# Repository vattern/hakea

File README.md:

# hakea

.

To flash the bootloader :
```
cd bootloader
openocd -f hakea.cfg
```

Current version : 1.0.4

This work is licensed under a
[Creative Commons Attribution-NonCommercial-ShareAlike 4.0 International License][cc-by-nc-sa].

[![CC BY-NC-SA 4.0][cc-by-nc-sa-image]][cc-by-nc-sa]

[cc-by-nc-sa]: http://creativecommons.org/licenses/by-nc-sa/4.0/
[cc-by-nc-sa-image]: https://licensebuttons.net/l/by-nc-sa/4.0/88x31.png
[cc-by-nc-sa-shield]: https://img.shields.io/badge/License-CC%20BY--NC--SA%204.0-lightgrey.svg

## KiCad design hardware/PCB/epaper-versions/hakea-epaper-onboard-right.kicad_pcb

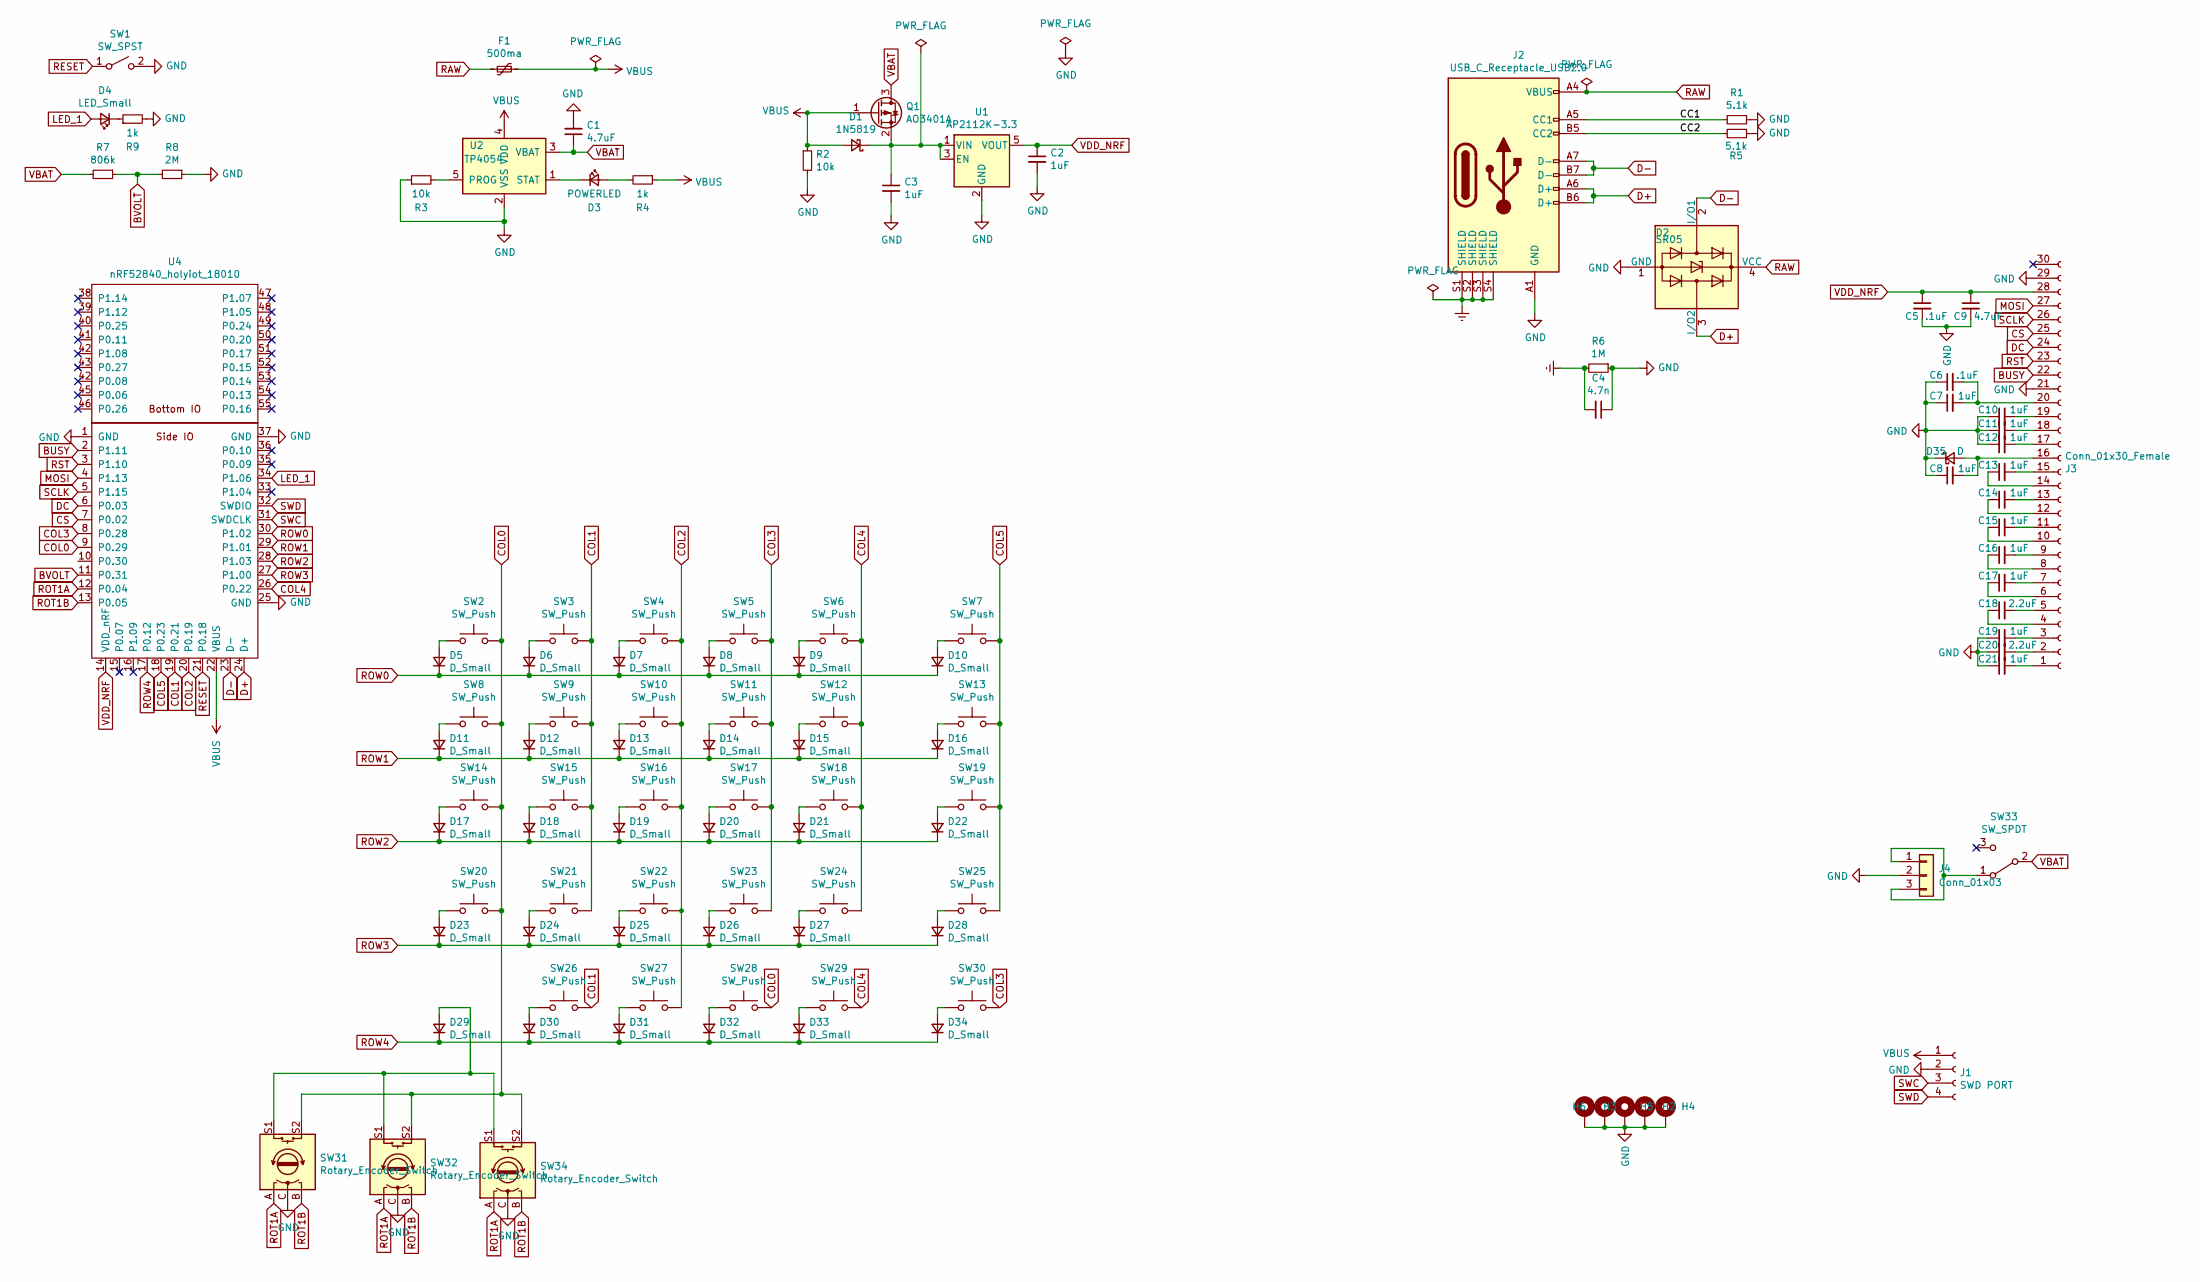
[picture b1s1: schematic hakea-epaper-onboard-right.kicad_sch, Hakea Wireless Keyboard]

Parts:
C1: 4.7uF; C_0805_2012Metric
C2, C3: 1uF; C_0805_2012Metric
C4: 4.7n; C_1206_3216Metric
C5, C6: .1uF; C_0402_1005Metric; LCSC C1525
C7, C8, C10, C11, C12, C13, C14, C15, C16, C17, C19, C21: 1uF; C_0402_1005Metric; LCSC C52923
C9: 4.7uF; C_0402_1005Metric; LCSC C23733
C18, C20: 2.2uF; C_0603_1608Metric; LCSC C23630
D1: 1N5819; D_SOD-123
D2: SR05; SOT-143
D3: POWERLED; D_0805_2012Metric
D4: LED_Small; D_0805_2012Metric
D5, D6, D7, D8, D9, D10, D11, D12, D13, D14, D15, D16, D17, D18, D19, D20, D21, D22, D23, D24, D25, D26, D27, D28, D29, D30, D31, D32, D33, D34: D_Small; D_SOD-123
D35: D; D_SOD-123; LCSC C8598
F1: 500ma; Fuse_1206_3216Metric
H2, H3, H4, H5, H6: MountingHole; MountingHole_2.2mm_M2_ISO7380_Pad
J1: SWD PORT; PinHeader_1x04_P2.54mm_Vertical
J2: USB_C_Receptacle_USB2.0; USB-C_C168688; LCSC Part C168688
J3: Conn_01x30_Female; Hirose_FH12-30S-0.5SH_1x30-1MP_P0.50mm_Horizontal; LCSC C262294
J4: Conn_01x03; JST_PH_S3B-PH-K_1x03_P2.00mm_Horizontal
Q1: AO3401A; SOT-23
R1, R5: 5.1k; R_0805_2012Metric
R2, R3: 10k; R_0805_2012Metric
R4, R9: 1k; R_0805_2012Metric
R6: 1M; R_0805_2012Metric
R7: 806k; R_0805_2012Metric
R8: 2M; R_0805_2012Metric
SW1: SW_SPST; TC-1101V
SW2, SW3, SW4, SW5, SW6, SW7, SW8, SW9, SW10, SW11, SW12, SW13, SW14, SW15, SW16, SW17, SW18, SW19, SW20, SW21, SW22, SW23, SW24, SW25, SW26, SW27, SW28, SW29, SW30: SW_Push; MX-1U-Hotswap
SW31, SW32: Rotary_Encoder_Switch; RollerEncoder_Panasonic_EVQWGD001
SW33: SW_SPDT; midmount_slide
SW34: Rotary_Encoder_Switch; RotaryEncoder_Alps_EC11E-Switch_Vertical_H20mm
U1: AP2112K-3.3; SOT-23-5
U2: TP4054; SOT-23-5
U4: nRF52840_holyiot_18010; nRF52840_holyiot_18010_copy

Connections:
/CC1: J2.A5 (CC1), R1.2
/CC2: J2.B5 (CC2), R5.2
BUSY: J3.22, U4.2 (P1.11)
BVOLT: R7.1, R8.2, U4.11 (P0.31)
COL0: SW2.2, SW8.2, SW14.2, SW20.2, SW28.2, SW31.S2, SW32.S2, SW34.S2, U4.9 (P0.29)
COL1: SW3.2, SW9.2, SW15.2, SW21.2, SW26.2, U4.19 (P0.21)
COL2: SW4.2, SW10.2, SW16.2, SW22.2, SW27.2, U4.20 (P0.19)
COL3: SW5.2, SW11.2, SW17.2, SW23.2, SW30.2, U4.8 (P0.28)
COL4: SW6.2, SW12.2, SW18.2, SW24.2, SW29.2, U4.26 (P0.22)
COL5: SW7.2, SW13.2, SW19.2, SW25.2, U4.18 (P0.23)
CS: J3.25, U4.7 (P0.02)
D+: D2.3 (I/O2), J2.A6 (D+), J2.B6 (D+), U4.24 (D+)
D-: D2.2 (I/O1), J2.A7 (D-), J2.B7 (D-), U4.23 (D-)
DC: J3.24, U4.6 (P0.03)
Earth: C4.2, J2.S1 (SHIELD), J2.S2 (SHIELD), J2.S3 (SHIELD), J2.S4 (SHIELD), R6.2
LED_1: D4.2 (A), U4.34 (P1.06)
MOSI: J3.27, U4.4 (P1.13)
unnamed: C3.1, D1.1 (K), Q1.2 (S), U1.1 (VIN), U1.3 (EN)
unnamed: C6.2, C7.2, J3.20
unnamed: C8.2, D35.2 (A), J3.16
unnamed: C10.2, J3.19
unnamed: C11.2, J3.18
unnamed: C12.2, J3.17
unnamed: C13.1, J3.14
unnamed: C13.2, J3.15
unnamed: C14.1, J3.12
unnamed: C14.2, J3.13
unnamed: C15.1, J3.10
unnamed: C15.2, J3.11
unnamed: C16.1, J3.8
unnamed: C16.2, J3.9
unnamed: C17.1, J3.6
unnamed: C17.2, J3.7
unnamed: C18.1, J3.4
unnamed: C18.2, J3.5
unnamed: C19.2, J3.3
unnamed: C21.2, J3.1
unnamed: D3.1 (K), U2.1 (STAT)
unnamed: D3.2 (A), R4.2
unnamed: D4.1 (K), R9.1
unnamed: D5.2 (A), SW2.1
unnamed: D6.2 (A), SW3.1
unnamed: D7.2 (A), SW4.1
unnamed: D8.2 (A), SW5.1
unnamed: D9.2 (A), SW6.1
unnamed: D10.2 (A), SW7.1
unnamed: D11.2 (A), SW8.1
unnamed: D12.2 (A), SW9.1
unnamed: D13.2 (A), SW10.1
unnamed: D14.2 (A), SW11.1
unnamed: D15.2 (A), SW12.1
unnamed: D16.2 (A), SW13.1
unnamed: D17.2 (A), SW14.1
unnamed: D18.2 (A), SW15.1
unnamed: D19.2 (A), SW16.1
unnamed: D20.2 (A), SW17.1
unnamed: D21.2 (A), SW18.1
unnamed: D22.2 (A), SW19.1
unnamed: D23.2 (A), SW20.1
unnamed: D24.2 (A), SW21.1
unnamed: D25.2 (A), SW22.1
unnamed: D26.2 (A), SW23.1
unnamed: D27.2 (A), SW24.1
unnamed: D28.2 (A), SW25.1
unnamed: D29.2 (A), SW31.S1, SW32.S1, SW34.S1
unnamed: D30.2 (A), SW26.1
unnamed: D31.2 (A), SW27.1
unnamed: D32.2 (A), SW28.1
unnamed: D33.2 (A), SW29.1
unnamed: D34.2 (A), SW30.1
unnamed: J4.1, J4.3, SW33.1 (A)
unnamed: R3.2, U2.5 (PROG)
RAW: D2.4 (VCC), F1.2, J2.A4 (VBUS)
RESET: SW1.1 (A), U4.21 (P0.18)
ROT1A: SW31.A, SW32.A, SW34.A, U4.12 (P0.04)
ROT1B: SW31.B, SW32.B, SW34.B, U4.13 (P0.05)
ROW0: D5.1 (K), D6.1 (K), D7.1 (K), D8.1 (K), D9.1 (K), D10.1 (K), U4.30 (P1.02)
ROW1: D11.1 (K), D12.1 (K), D13.1 (K), D14.1 (K), D15.1 (K), D16.1 (K), U4.29 (P1.01)
ROW2: D17.1 (K), D18.1 (K), D19.1 (K), D20.1 (K), D21.1 (K), D22.1 (K), U4.28 (P1.03)
ROW3: D23.1 (K), D24.1 (K), D25.1 (K), D26.1 (K), D27.1 (K), D28.1 (K), U4.27 (P1.00)
ROW4: D29.1 (K), D30.1 (K), D31.1 (K), D32.1 (K), D33.1 (K), D34.1 (K), U4.17 (P0.12)
RST: J3.23, U4.3 (P1.10)
SCLK: J3.26, U4.5 (P1.15)
SWC: J1.3, U4.31 (SWDCLK)
SWD: J1.4, U4.32 (SWDIO)
VBUS: D1.2 (A), F1.1, J1.1, Q1.1 (G), R2.1, R4.1, U2.4 (VDD), U4.22 (VBUS)
VDD_NRF: C2.1, C5.1, C9.1, J3.28, U1.5 (VOUT), U4.14 (VDD_nRF)

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
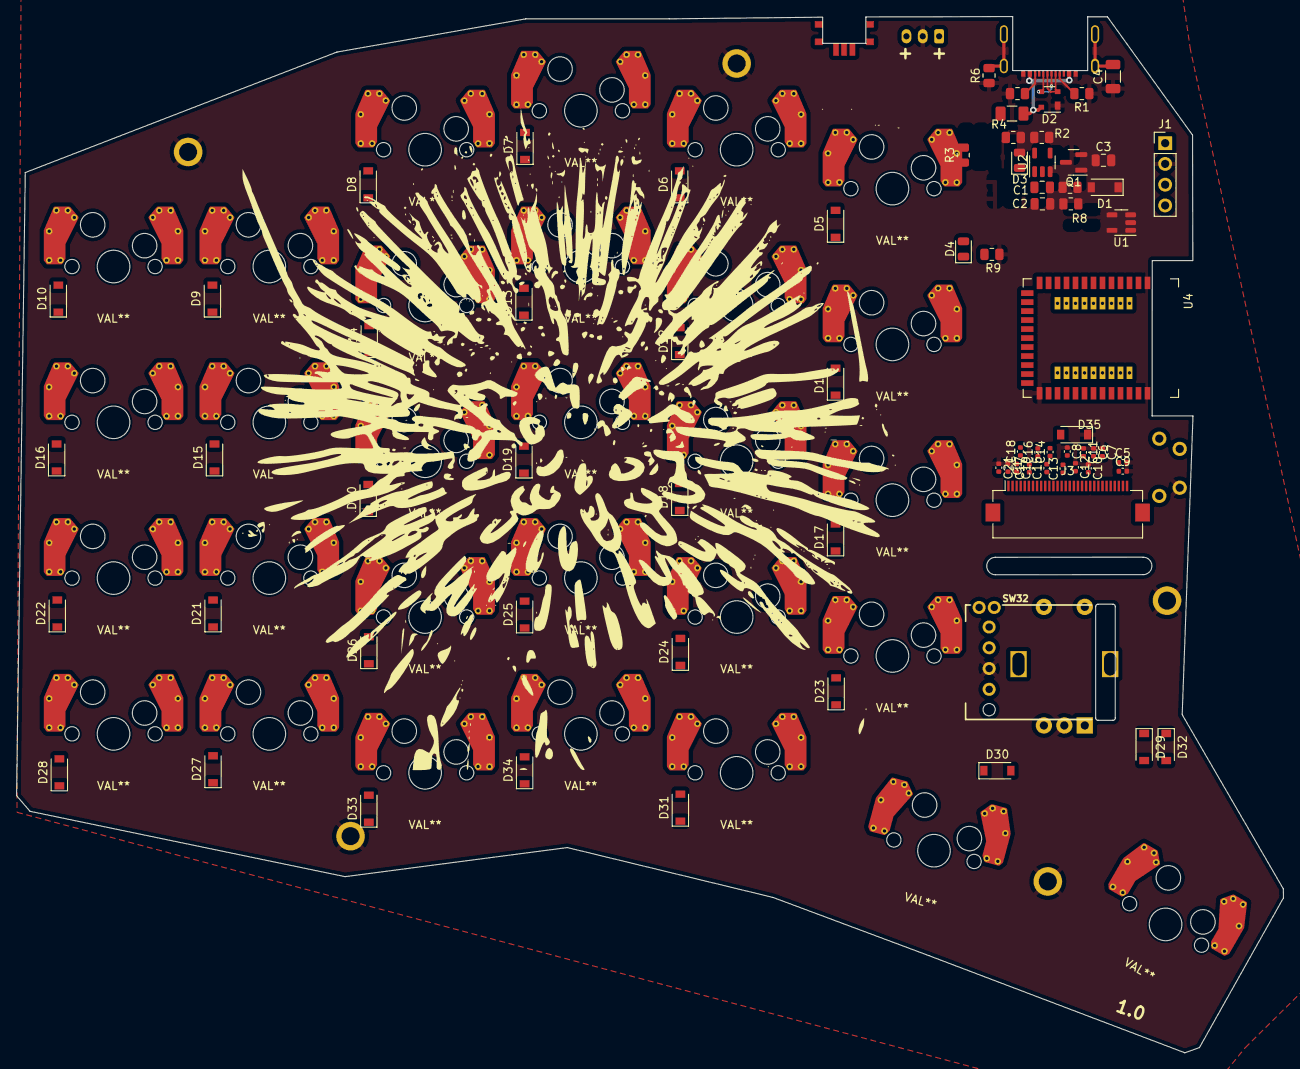
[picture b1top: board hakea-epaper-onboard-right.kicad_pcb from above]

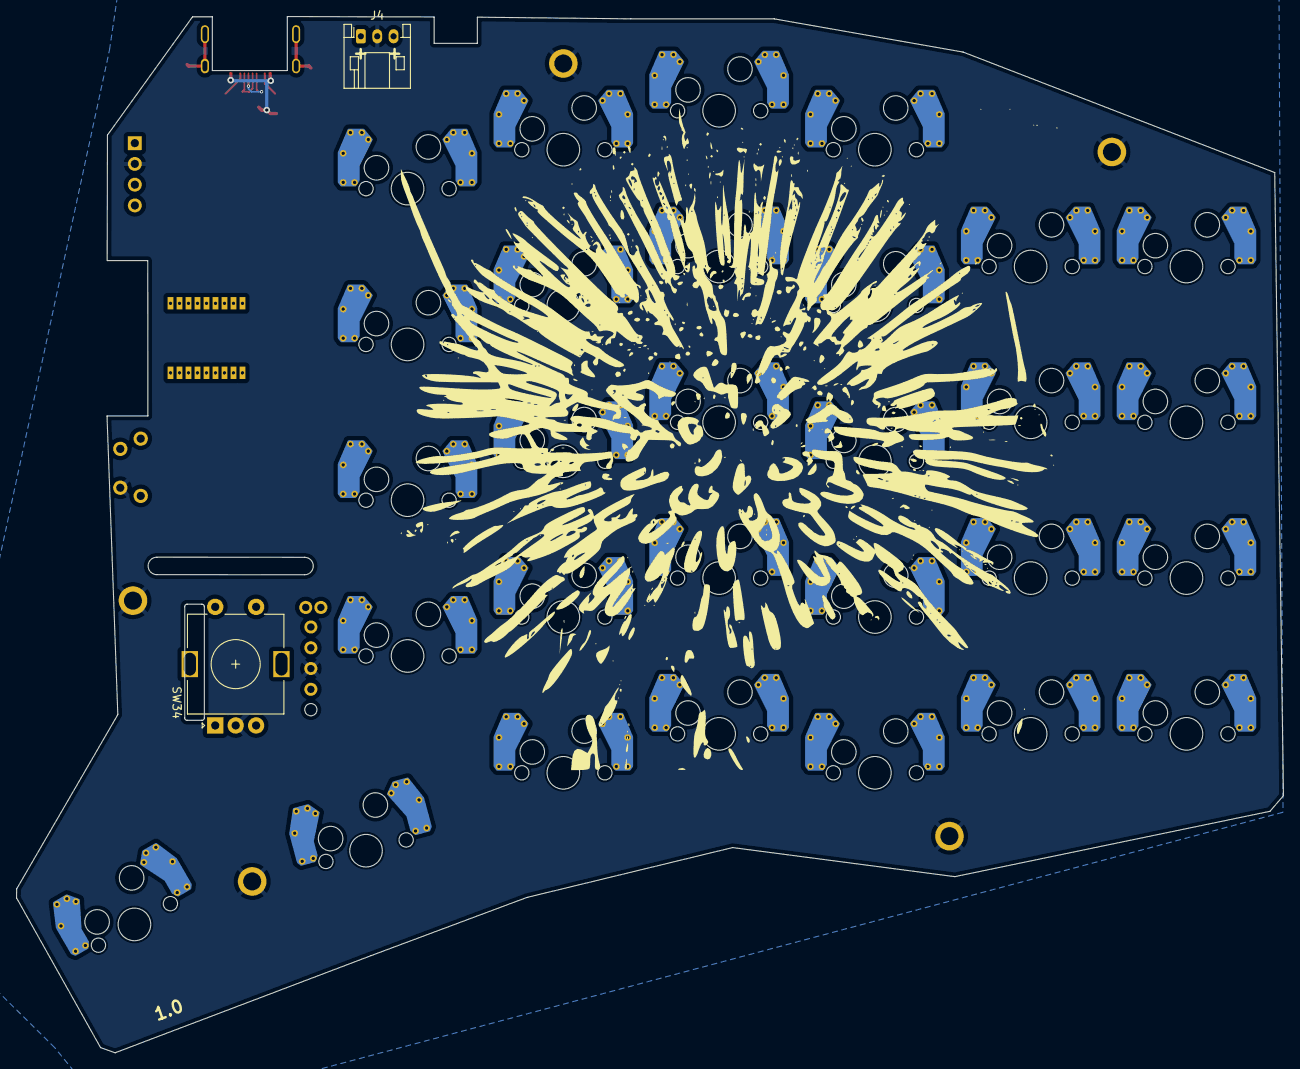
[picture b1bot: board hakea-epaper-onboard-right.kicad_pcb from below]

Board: 2 copper layers, 154.9 x 126.7 mm, 112 parts (7 on the bottom side), 90 nets.

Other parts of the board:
C1#2: 4.7uF; C_0805_2012Metric

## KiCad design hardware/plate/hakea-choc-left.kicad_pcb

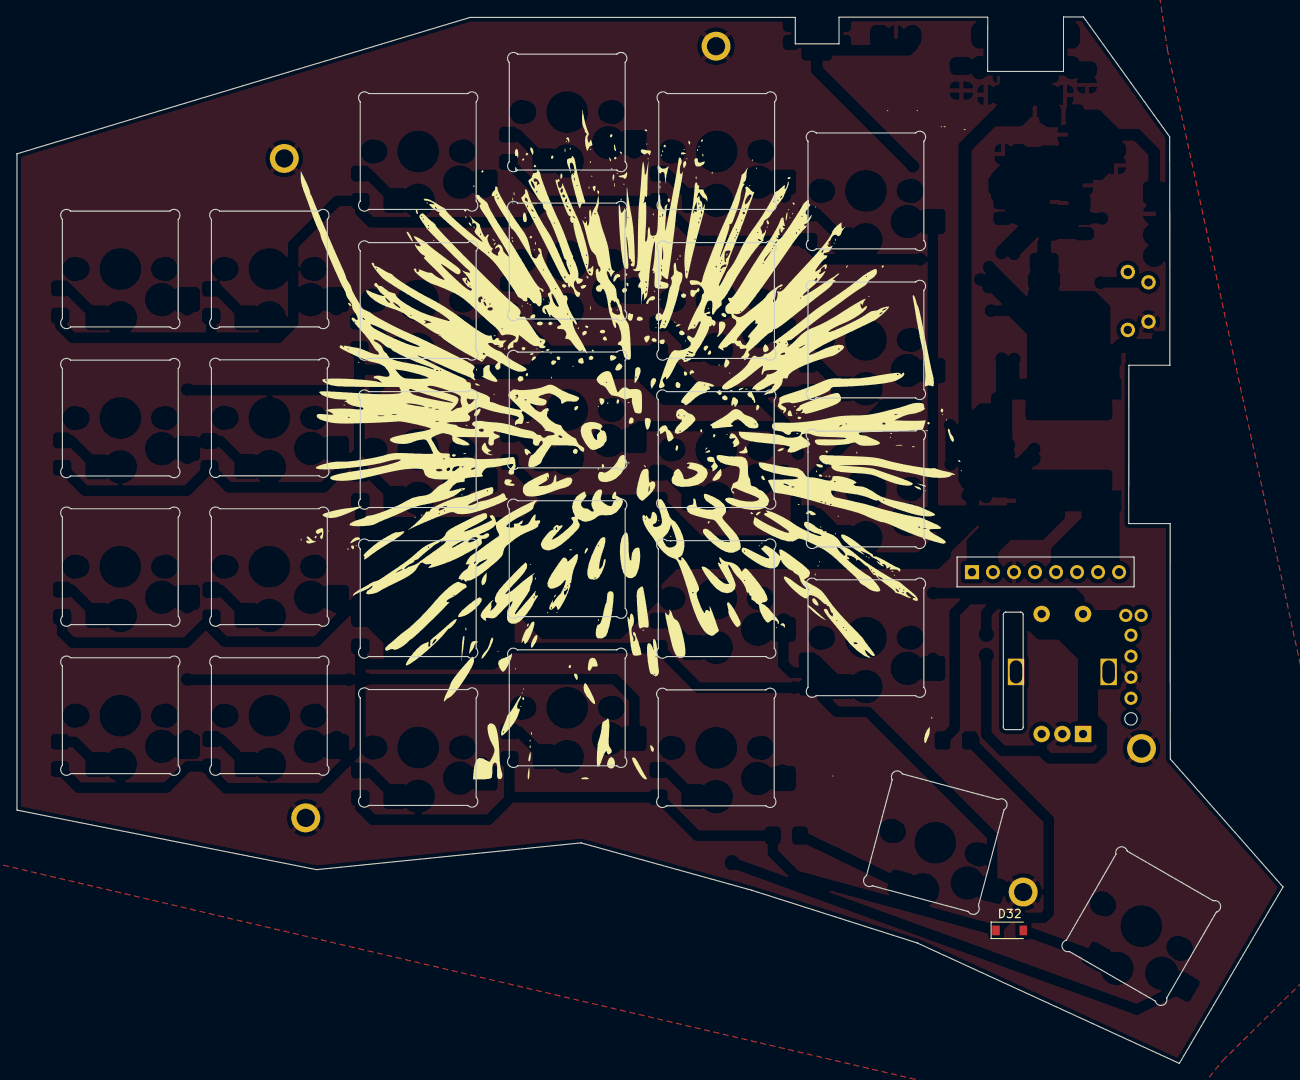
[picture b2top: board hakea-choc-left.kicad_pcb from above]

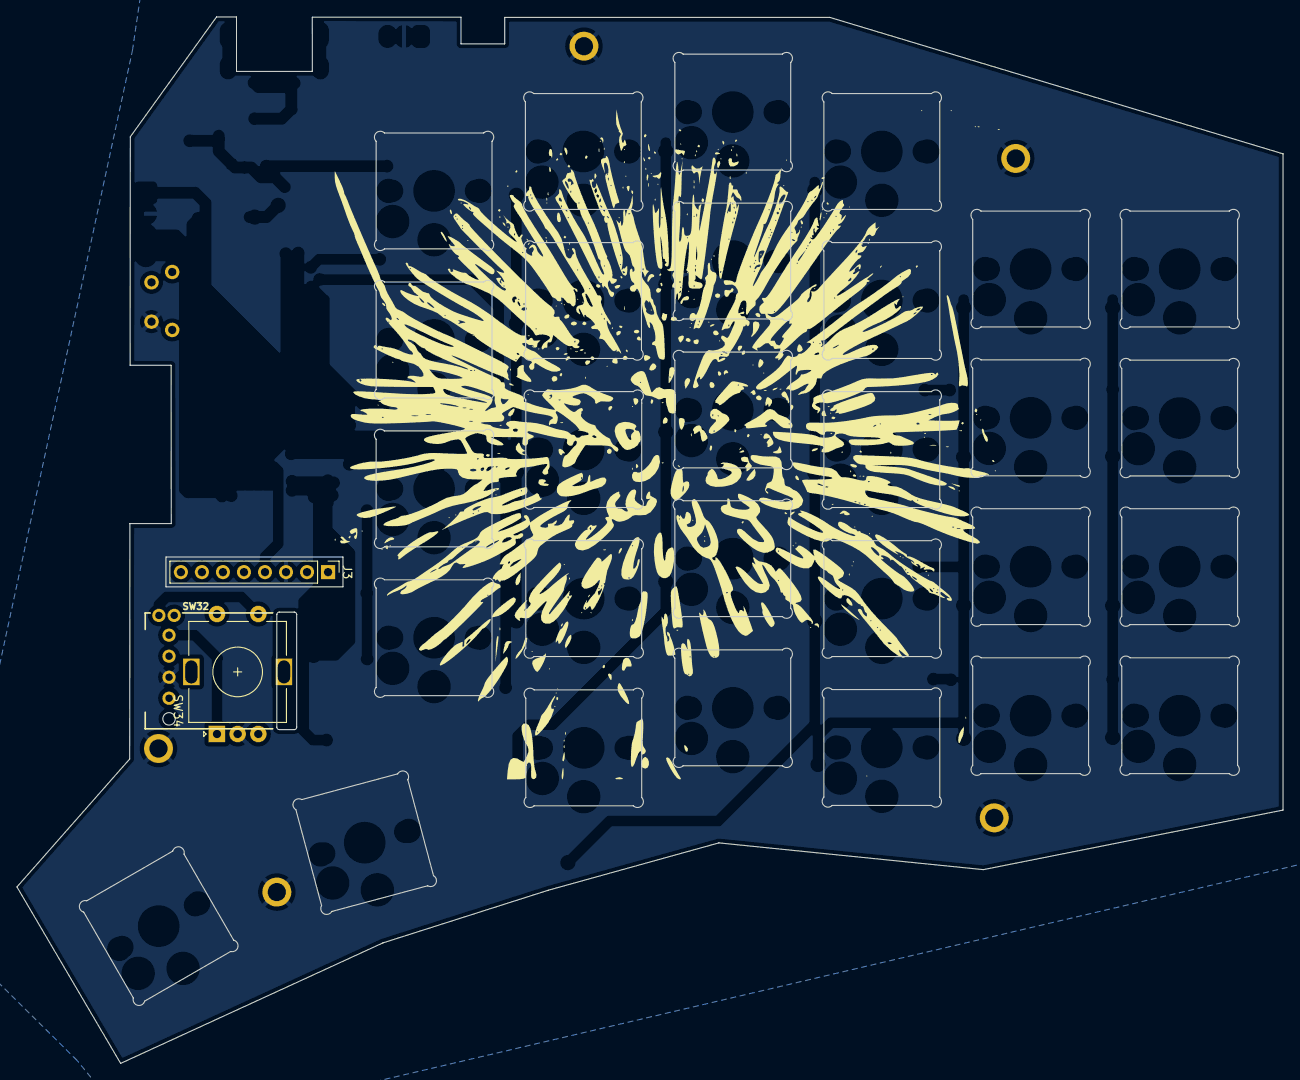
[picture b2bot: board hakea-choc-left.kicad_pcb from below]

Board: 2 copper layers, 153.0 x 126.4 mm, 39 parts (9 on the bottom side), 5 nets, no tracks yet.

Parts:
D32: D_Small; D_SOD-123
H2, H3, H4, H5, H6: MountingHole; MountingHole_2.2mm_M2_ISO7380_Pad
J3: epaper-102; PinHeader_1x08_P2.54mm_Vertical
SW1: SW_SPST; TC-1101V
SW2, SW3, SW4, SW5, SW6, SW7, SW8, SW9, SW10, SW11, SW12, SW13, SW14, SW15, SW16, SW17, SW18, SW19, SW20, SW21, SW22, SW23, SW24, SW25, SW26, SW27, SW28, SW29, SW30: SW_Push; MX-1U-PlateCutout
SW32: Rotary_Encoder_Switch; RollerEncoder_Panasonic_EVQWGD001
SW34: Rotary_Encoder_Switch; RotaryEncoder_Alps_EC11E-Switch_Vertical_H20mm

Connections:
COL0: SW32.S2, SW34.S2
GND: H2.1, H3.1, H4.1, H5.1, H6.1, J3.3, SW1.2 (B), SW32.C, SW34.C
unnamed: SW32.S1, SW34.S1
ROT1A: SW32.A, SW34.A
ROT1B: SW32.B, SW34.B

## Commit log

2022-01-09 Adding PCB's
2022-01-09 Add keymap submodule
2022-01-09 Updates with license
2022-01-09 supdate
2022-01-09 Latest
2022-01-30 choco
2022-02-02 Add Choc PCB
2023-08-10 Start adding workflow
2023-08-10 Poke vars
2023-08-10 Add changes [ci skip]
2023-08-10 Deploying to main from @ vattern/hakea@3202aff9c39c4f6871eb6f568053452fa9e7f84b 🚀
2023-08-11 Poke workflow
2023-08-11 Deploying to main from @ vattern/hakea@a5b96a3654e8c4c2cad9a5c0fc8518ceaa60bf60 🚀
2023-08-11 add models:
2023-08-11 Add models for real
2023-08-11 Deploying to main from @ vattern/hakea@07888adfc4d3d05e36da48e5fa41e44ffbc609ec 🚀
2023-08-11 Generifiy workflow:
2023-08-11 Add encoder
2023-08-11 Deploying to main from @ vattern/hakea@adbe2e82a033bb924f23cdc9d65d69e42ec41da4 🚀
2023-08-12 Deploying to main from @ vattern/hakea@c7dcee189fded335dc598b0622f875cdaedd3d09 🚀
2023-08-12 Deploying to main from @ vattern/hakea@7c61a6dcedec190f9d44303eac4ef9cf64878c7a 🚀
